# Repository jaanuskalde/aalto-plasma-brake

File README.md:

Aalto-1 Electrical Plasma Brake software and hardware
============================================

Hardware is done in EagleCAD 6.
Software is done in Code Composer Studio.

jaanus@tech-thing.org
2013

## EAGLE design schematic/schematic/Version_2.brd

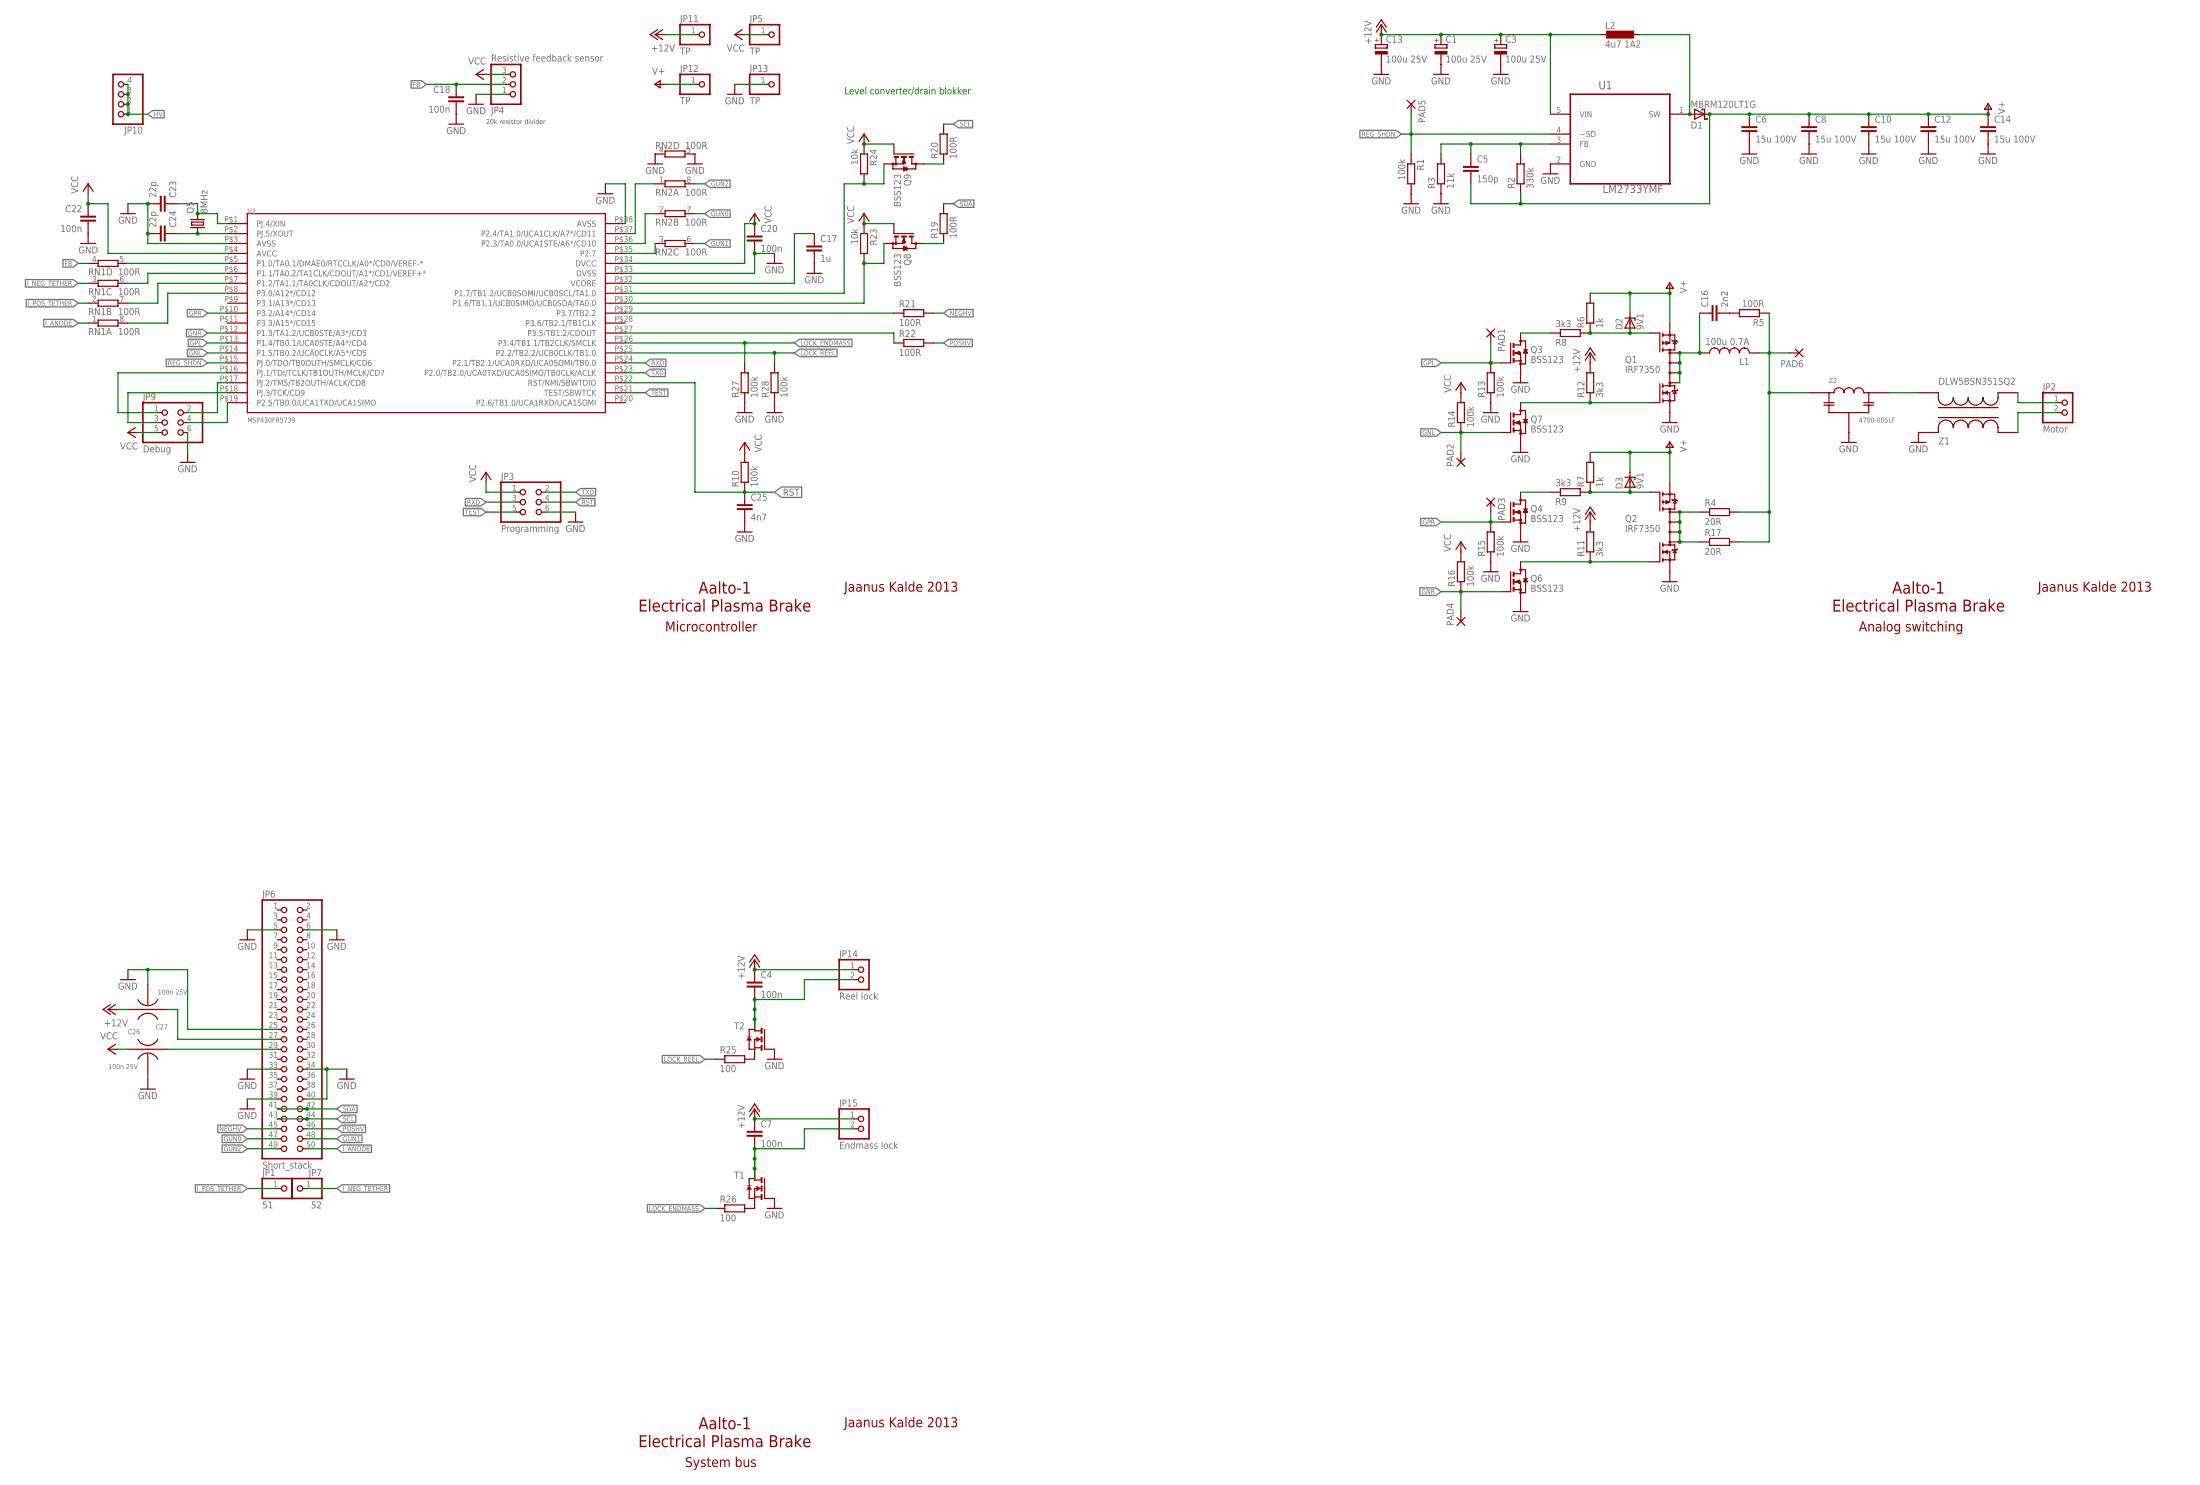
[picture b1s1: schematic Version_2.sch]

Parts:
C1, C3, C13: 100u 25V; SMC_E
C4, C7, C22: 100n; C0603
C5: 150p; C0603K
C6, C8, C10, C12, C14: 15u 100V; C2220K
C16: 2n2; C0805
C17: 1u; C0603K
C18, C20: 100n; C0603K
C23, C24: 22p; C0603
C25: 4n7; C0603
C26, C27: 100n 25V; 0805-3TERM
D1: MBRM120LT1G; POWERMITE
D2, D3: 9V1; SOD80C
JP1: 51; 1X01
JP2: Motor; 1X02M
JP3: Programming; MICROMATCH-6
JP4: Resistive feedback sensor; 1X03M
JP5, JP11, JP12, JP13: TP; 1X01
JP6: Short_stack; 2X25
JP7: 52; 1X01
JP9: Debug; MICROMATCH-6
JP10: PINHD-1X4; 1X04
JP14: Reel lock; 1X02M
JP15: Endmass lock; 1X02M
L1: 100u 0.7A; L-SMD-7.3
L2: 4u7 1A2; SRR4011
PAD1, PAD2, PAD3, PAD4, PAD5, PAD6: WIREPAD1,6/0,8; 1,6/0,8
Q1, Q2: IRF7350; SO08-IRF
Q3, Q4, Q6, Q7, Q8, Q9: BSS123; SOT23
Q5: 8MHz; HC49U-V
R1, R10, R13, R14, R15, R16, R27, R28: 100k; R0603
R2: 330k; R0603
R3: 11k; R0603
R4, R17: 20R; R2512
R5: 100R; R0805
R6, R7: 1k; R0805
R8, R9, R11, R12: 3k3; R0805
R19, R20, R21, R22: 100R; R0603
R23, R24: 10k; R0603
R25, R26: 100; R0603
RN1, RN2: 100R; EXBN8V
T1, T2: NMOSSOT23-6; SOT23-6
U1: LM2733YMF; SOT95P284X119-5N
U2: MSP430FR5739; TSSOP38
Z1: DLW5BSN351SQ2; DLW5BS
Z2: 4700-005LF; FILTER-PI

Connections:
+12V: C1.+, C3.+, C4.1, C7.1, C13.+, C26.P$1, JP11.1, JP14.1, JP15.1, L2.P$1 (1), R11.2, R12.2, U1.5 (VIN)
CLK: JP9.3, U2.P$18 (PJ.3/TCK/CD9)
FB: C18.1, JP4.2, RN1.4 (1)
FBBBBBA: C5.1, R2.2, R3.2, U1.3 (FB)
GND: C1.-, C3.-, C6.2, C8.2, C10.2, C12.2, C13.-, C14.2, C17.2, C18.2, C20.2, C22.2, C23.2, C24.2, C25.2, C26.P$2, C27.P$2, JP3.6, JP4.1, JP6.5, JP6.6, JP6.25, JP6.33, JP6.34, JP6.39, JP6.40, JP9.6, JP13.1, Q1.1 (N-S), Q2.1 (N-S), Q3.2 (S), Q4.2 (S), Q6.2 (S), Q7.2 (S), R1.2, R3.1, R13.1, R15.1, R27.1, R28.1, RN2.4 (1), RN2.5 (2), T1.4 (G), T2.4 (G), U1.2 (GND), U2.P$3 (AVSS), U2.P$33 (DVSS), U2.P$38 (AVSS), Z1.P$2, Z2.P$2
GNL: PAD2.1, Q7.1 (G), R14.1, U2.P$14 (P1.5/TB0.2/UCA0CLK/A5*/CD5)
GNR: PAD4.1, Q6.1 (G), R16.1, U2.P$12 (P1.3/TA1.2/UCB0STE/A3*/CD3)
GPL: PAD1.1, Q3.1 (G), R13.2, U2.P$13 (P1.4/TB0.1/UCA0STE/A4*/CD4)
GPR: PAD3.1, Q4.1 (G), R15.2, U2.P$10 (P3.2/A14*/CD14)
GUN0: JP6.47, RN2.7 (2)
GUN1: JP6.48, RN2.6 (2)
GUN2: JP6.49, RN2.8 (2)
HV: JP10.1, JP10.2, JP10.3, JP10.4
I_ANODE: JP6.50, RN1.1
I_NEG_TETHER: JP7.1, RN1.3 (1)
I_POS_TETHER: JP1.1, RN1.2 (1)
LOCK_ENDMASS: R26.1, R27.2, U2.P$26 (P3.4/TB1.1/TB2CLK/SMCLK)
LOCK_REEL: R25.1, R28.2, U2.P$25 (P2.2/TB2.2/UCB0CLK/TB1.0)
MISO/RX: JP9.2, U2.P$17 (PJ.2/TMS/TB2OUTH/ACLK/CD8)
unnamed: Q2.2 (N-G), Q6.3 (D), R11.1
unnamed: C7.2, JP15.2, T1.1 (D), T1.2 (D1), T1.5 (D2), T1.6 (D3)
unnamed: R26.2, T1.3 (S)
unnamed: C17.1, U2.P$32 (VCORE)
unnamed: RN1.5 (2), U2.P$5 (P1.0/TA0.1/DMAE0/RTCCLK/A0*/CD0/VEREF-*)
unnamed: Q1.2 (N-G), Q7.3 (D), R12.1
unnamed: C26.P$3, JP6.27
unnamed: D1.2 (A), L2.P$2 (2), U1.1 (SW)
unnamed: C4.2, JP14.2, T2.1 (D), T2.2 (D1), T2.5 (D2), T2.6 (D3)
unnamed: R25.2, T2.3 (S)
unnamed: Q9.3 (D), R20.1
unnamed: Q8.3 (D), R19.1
unnamed: C16.2, R5.2
unnamed: C16.1, L1.P$1 (1), Q1.5 (D), Q1.6 (D), Q1.7 (D), Q1.8 (D)
unnamed: L1.P$2 (2), PAD6.1, R4.2, R5.1, R17.2, Z2.P$1
unnamed: Q2.5 (D), Q2.6 (D), Q2.7 (D), Q2.8 (D), R4.1, R17.1
unnamed: C27.P$1, JP6.29
unnamed: Q9.2 (S), R24.2, U2.P$31 (P1.7/TB1.2/UCB0SOMI/UCB0SCL/TA1.0)
unnamed: D2.A, Q1.4 (P-G), R6.1, R8.2
unnamed: Z1.P$3, Z2.P$3
unnamed: D3.A, Q2.4 (P-G), R7.1, R9.2
unnamed: JP2.1, Z1.P$4
unnamed: Q3.3 (D), R8.1
unnamed: Q4.3 (D), R9.1
unnamed: R22.1, U2.P$27 (P3.5/TB1.2/CDOUT)
unnamed: C23.1, Q5.2, U2.P$1 (PJ.4/XIN)
unnamed: C24.1, Q5.1, U2.P$2 (PJ.5/XOUT)
unnamed: RN1.6 (2), U2.P$6 (P1.1/TA0.2/TA1CLK/CDOUT/A1*/CD1/VEREF+*)
unnamed: RN2.1, U2.P$37 (P2.4/TA1.0/UCA1CLK/A7*/CD11)
unnamed: R21.1, U2.P$29 (P3.7/TB2.2)
unnamed: Q8.2 (S), R23.2, U2.P$30 (P1.6/TB1.1/UCB0SIMO/UCB0SDA/TA0.0)
unnamed: RN1.7 (2), U2.P$7 (P1.2/TA1.1/TA0CLK/CDOUT/A2*/CD2)
unnamed: JP2.2, Z1.P$1
unnamed: RN1.8 (2), U2.P$8 (P3.0/A12*/CD12)
unnamed: RN2.2 (1), U2.P$36 (P2.3/TA0.0/UCA1STE/A6*/CD10)
unnamed: RN2.3 (1), U2.P$35 (P2.7)
unnamed: JP9.1, U2.P$16 (PJ.1/TDI/TCLK/TB1OUTH/MCLK/CD7)
NEGHV: JP6.45, R21.2
POSHV: JP6.46, R22.2
REG_SHDN: PAD5.1, R1.1, U1.4 (~SD), U2.P$15 (PJ.0/TDO/TB0OUTH/SMCLK/CD6)
RST: C25.1, JP3.4, R10.1, U2.P$22 (RST/NMI/SBWTDIO)
RXD: JP3.3, U2.P$24 (P2.1/TB2.1/UCA0RXD/UCA0SOMI/TB0.0)
SCL: JP6.43, JP6.44, R20.2
SDA: JP6.41, JP6.42, R19.2
SLAVE: JP9.4, U2.P$19 (P2.5/TB0.0/UCA1TXD/UCA1SIMO)
TEST: JP3.5, U2.P$21 (TEST/SBWTCK)
TXD: JP3.2, U2.P$23 (P2.0/TB2.0/UCA0TXD/UCA0SIMO/TB0CLK/ACLK)
V+: C5.2, C6.1, C8.1, C10.1, C12.1, C14.1, D1.1 (C), D2.C, D3.C, JP12.1, Q1.3 (P-S), Q2.3 (P-S), R2.1, R6.2, R7.2
VCC: C20.1, C22.1, C27.P$3, JP3.1, JP4.3, JP5.1, JP9.5, Q8.1 (G), Q9.1 (G), R10.2, R14.2, R16.2, R23.1, R24.1, U2.P$4 (AVCC), U2.P$34 (DVCC)

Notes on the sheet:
20k resistor divider
Jaanus Kalde 2013
Aalto-1 Electrical Plasma Brake
Microcontroller
Analog switching
System bus
Level converter/drain blokker

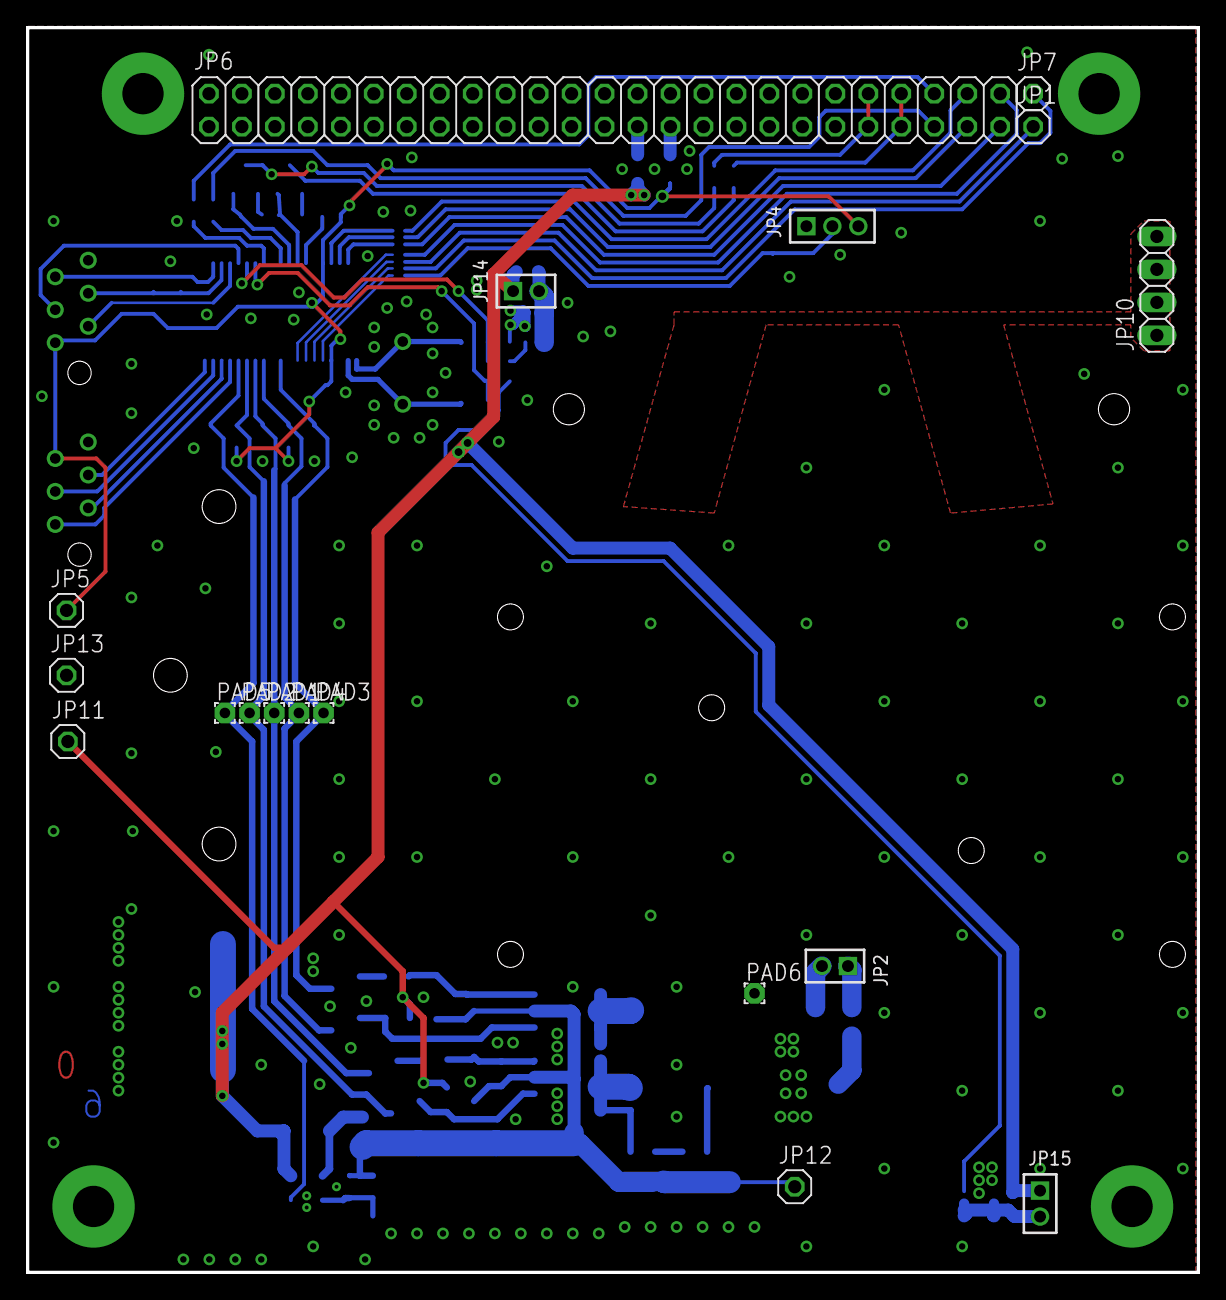
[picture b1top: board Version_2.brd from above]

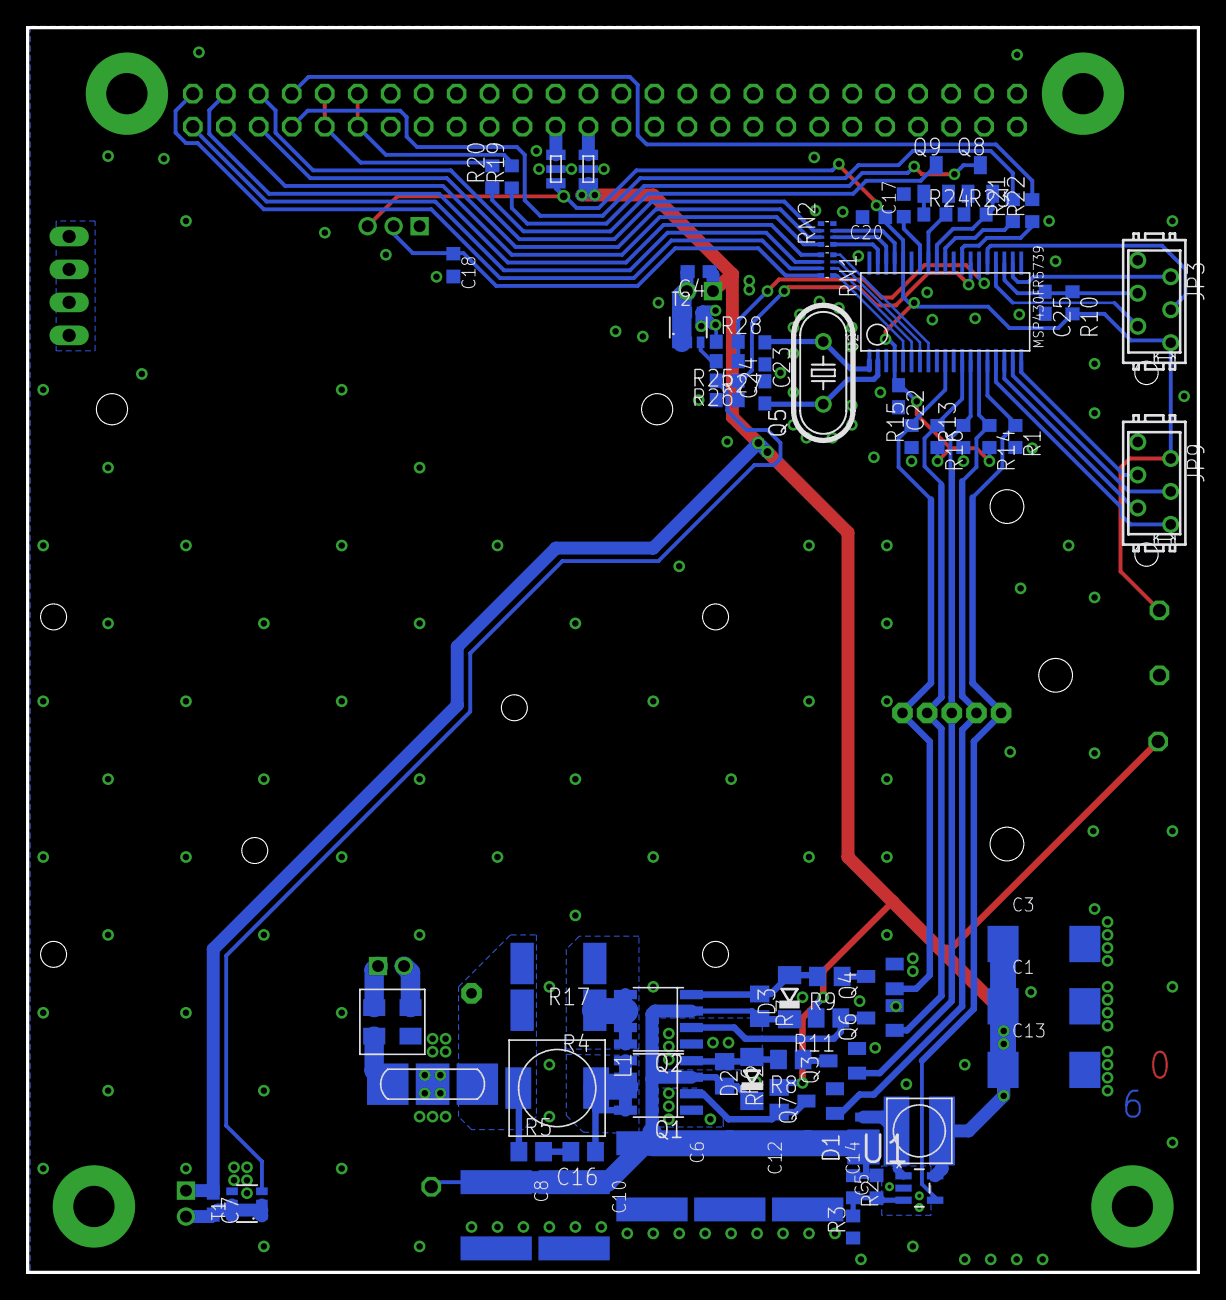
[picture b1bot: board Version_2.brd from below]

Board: 2 copper layers, 90.2 x 95.9 mm, 90 parts (72 on the bottom side), 68 nets.

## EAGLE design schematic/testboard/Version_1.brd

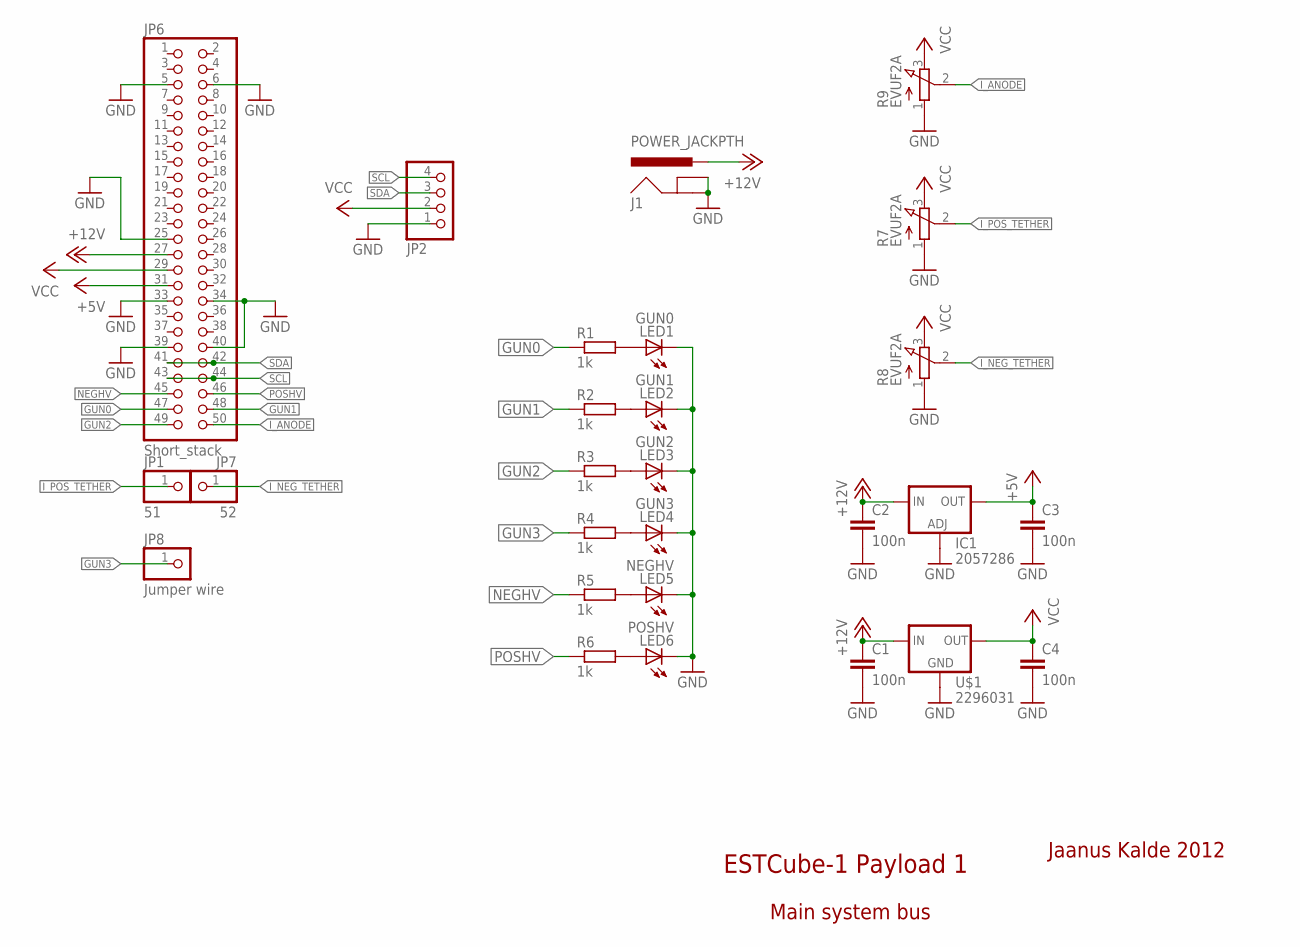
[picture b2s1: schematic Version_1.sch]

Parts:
C1, C2, C3, C4: 100n; C0603K
IC1: 2057286; SOT223
J1: POWER_JACKPTH; POWER_JACK_PTH
JP1: 51; 1X01
JP2: PINHD-1X4; 1X04
JP6: Short_stack; 2X25
JP7: 52; 1X01
JP8: Jumper wire; 1X01
LED1: GUN0; LED-0603
LED2: GUN1; LED-0603
LED3: GUN2; LED-0603
LED4: GUN3; LED-0603
LED5: NEGHV; LED-0603
LED6: POSHV; LED-0603
R1, R2, R3, R4, R5, R6: 1k; R0603
R7, R8, R9: EVUF2A; EVUF
U$1: 2296031; SOT223

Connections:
+5V: C3.1, IC1.4 (OUT), JP6.31
+12V: C1.1, C2.1, IC1.3 (IN), J1.PWR, JP6.27, U$1.1 (IN)
GND: C1.2, C2.2, C3.2, C4.2, IC1.1 (ADJ), J1.GND, J1.GNDBREAK, JP2.1, JP6.5, JP6.6, JP6.25, JP6.33, JP6.34, JP6.39, JP6.40, LED1.C, LED2.C, LED3.C, LED4.C, LED5.C, LED6.C, R7.1 (A), R8.1 (A), R9.1 (A), U$1.2 (GND)
GUN0: JP6.47, R1.1
GUN1: JP6.48, R2.1
GUN2: JP6.49, R3.1
GUN3: JP8.1, R4.1
I_ANODE: JP6.50, R9.2 (S)
I_NEG_TETHER: JP7.1, R8.2 (S)
I_POS_TETHER: JP1.1, R7.2 (S)
unnamed: LED1.A, R1.2
unnamed: LED2.A, R2.2
unnamed: LED3.A, R3.2
unnamed: LED4.A, R4.2
unnamed: LED5.A, R5.2
unnamed: LED6.A, R6.2
NEGHV: JP6.45, R5.1
POSHV: JP6.46, R6.1
SCL: JP2.4, JP6.43, JP6.44
SDA: JP2.3, JP6.41, JP6.42
VCC: C4.1, JP2.2, JP6.29, R7.3 (E), R8.3 (E), R9.3 (E), U$1.3 (OUT)

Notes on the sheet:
Jaanus Kalde 2012
ESTCube-1 Payload 1
Main system bus

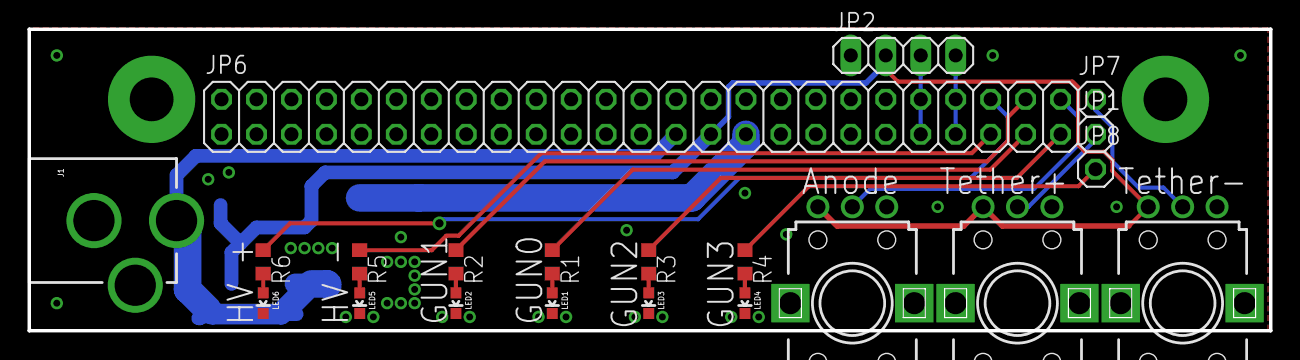
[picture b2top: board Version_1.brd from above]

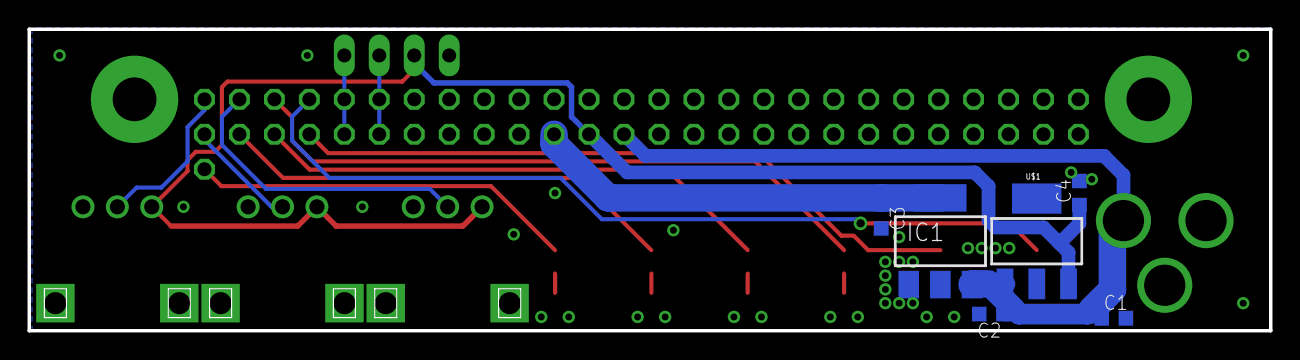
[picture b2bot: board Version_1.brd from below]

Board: 2 copper layers, 90.2 x 21.9 mm, 27 parts (6 on the bottom side), 21 nets.

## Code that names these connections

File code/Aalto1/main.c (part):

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#define GATE_N_RESISTOR 0x08	//PORT1
#define GATE_P_INDUCTOR 0x10	//PORT1
#define GATE_N_INDUCTOR 0x20	//PORT1
#define LOCK_ENDMASS 0x10	//PORT3
#define LOCK_REEL 0x04	//PORT2
#define FB 0x01		//PORT1
#define BOOST 0x01	//PORTJ

//Pins for high voltage board.
#define I_NEG 0x02	//PORT1
#define I_POS 0x04	//PORT1
#define I_ANODE 0x01	//PORT3
#define EMITTER0 0x08	//PORT2
#define EMITTER1 0x80	//PORT2
#define EMITTER2 0x10	//PORT2
#define EMITTER3 0x02	//PORT3
#define NEGHV 0x80	//PORT3
#define POSHV 0x20	//PORT3

//It's the one guy!

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
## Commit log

2013-10-29 Old repo and latest code in Aalto.
2014-02-03 V2.0

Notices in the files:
parts and their libraries:
SparkFun: Licensing: CC v3.0 Share-Alike You are welcome to use this library for commercial purposes.
